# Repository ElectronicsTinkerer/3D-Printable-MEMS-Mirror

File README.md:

# 3D-Printable-MEMS-Mirror
Files for a 3D-printable MEMS mirror.

## Files
* `models` - SolidWorks files for parts
* `stls` - STL files for printing
* `arduino` - Arduino controller code
* `kicad` - PCB files (and gerbers)

## Online Resources
* [MDPI Books, _MEMS Mirrors_ ](https://www.mdpi.com/books/pdfview/book/611) - Great PDF of a lot of different MEMS mirrors designs and analysis.
* Shopping (For commercial MEMS Mirrors):
  * [Mirrorcle Technologies Inc.](https://www.mirrorcletech.com/wp/products/mems-mirrors/) - Has pricing info
  * [Preciseley Microtechnology Corp.](https://preciseley.com/products/) - Even has development hats for RPi!
  * [Hamamatsu](https://www.hamamatsu.com/us/en/product/optical-components/mems-mirror/index.html)

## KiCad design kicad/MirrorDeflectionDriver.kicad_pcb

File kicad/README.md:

# Axis Drivers for Mirrors

## Interface
### Power
Each board has a 16-30v DC, single rail input. This is the operating voltage of the output amplifiers.

### Output
At the end of the board is the output terminal block to be connected to one of the yoke's deflection coils.

### Digital Interface
At the other end is a parallel interface header for sending data to the DAC. The DAC operates over a 5v interface and all connections have 10k pullup resistors, meaning that unused inputs can be left unconnected. There is a 12-bit parallel data bus, read/write, chip select, reset, and load inputs.

## Output Drive Design
In order to achieve a differential output, two output amplifiers are used, one the inversion of the other around 0.5 * VCC.

## Known Issues
* The heatsinks currently on the KiCad boards are inadequate for the output amplifiers if running at greater than about 0.5A output current. (Active cooling is required)
* The 2.5V regulator's pinning is rotated 120 degrees clockwise from what it should be, so check the datasheet and schematic before soldering. This should be fixed some time in the future.

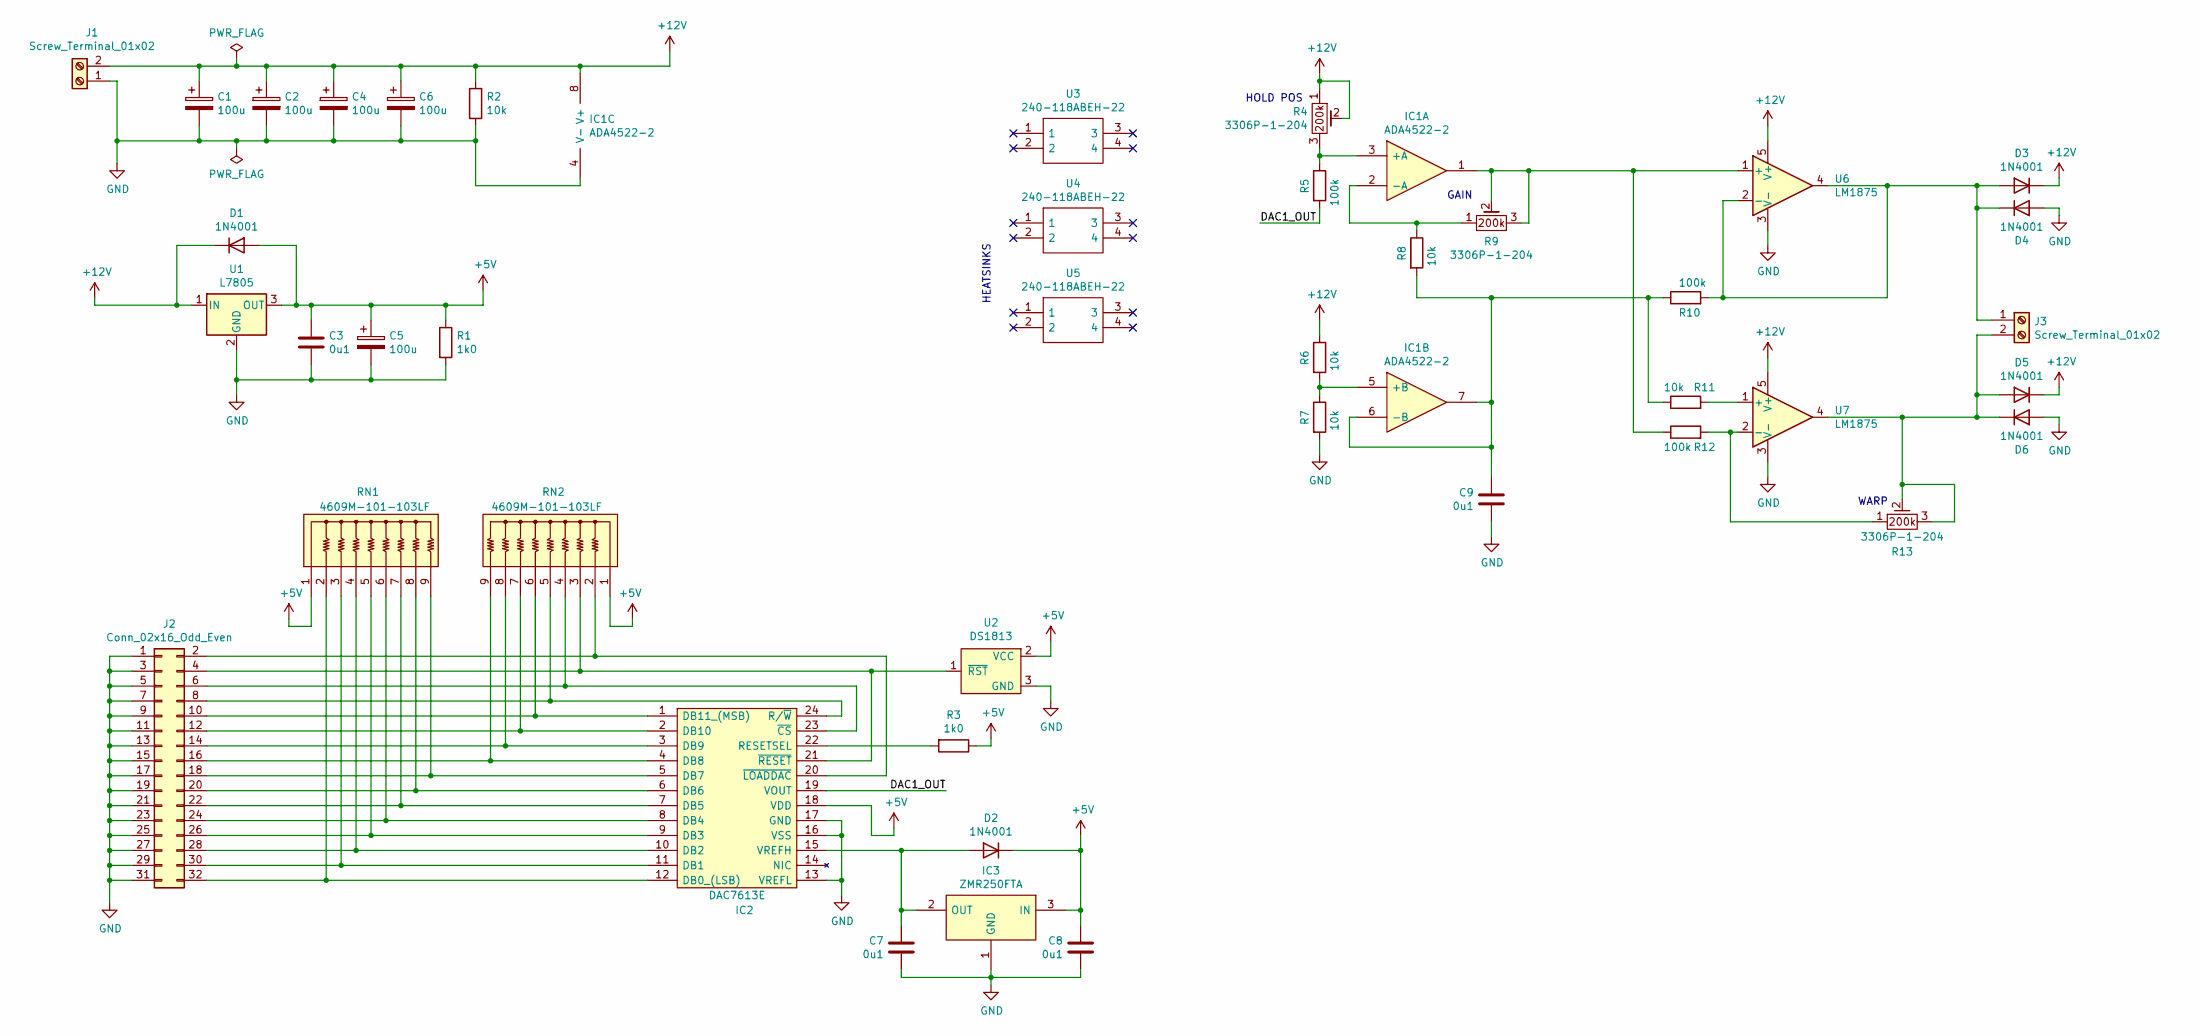
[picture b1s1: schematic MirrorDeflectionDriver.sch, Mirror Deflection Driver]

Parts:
C1, C2, C4, C5, C6: 100u; CP_Radial_D8.0mm_P3.50mm
C3, C7, C8, C9: 0u1; C_Disc_D4.3mm_W1.9mm_P5.00mm
D1, D2, D3, D4, D5, D6: 1N4001; D_DO-41_SOD81_P10.16mm_Horizontal
IC1: ADA4522-2; MSOP-8_3x3mm_P0.65mm; Mouser Part Number 584-ADA4522-2
IC2: DAC7613E; SOP65P780X200-24N; Mouser Part Number 595-DAC7613E
IC3: ZMR250FTA; SOT96P240X100-3N; Mouser Part Number 522-ZMR250FTA
J1, J3: Screw_Terminal_01x02; TerminalBlock_bornier-2_P5.08mm
J2: Conn_02x16_Odd_Even; PinHeader_2x16_P2.54mm_Vertical
R1, R3: 1k0; R_Axial_DIN0207_L6.3mm_D2.5mm_P7.62mm_Horizontal
R2, R6, R7, R8, R11: 10k; R_Axial_DIN0207_L6.3mm_D2.5mm_P7.62mm_Horizontal
R4, R9, R13: 3306P-1-204; 3306P1204; Mouser Part Number 652-3306P-1-204
R5, R10, R12: 100k; R_Axial_DIN0207_L6.3mm_D2.5mm_P7.62mm_Horizontal
RN1, RN2: 4609M-101-103LF; 4609X; Mouser Part Number 652-4609M-1LF-10K
U1: L7805; TO-126-3_Vertical
U2: DS1813; TO-92
U3, U4, U5: 240-118ABEH-22; 240118ABEH22; Mouser Part Number 567-240-118ABH-22
U6, U7: LM1875; TO-220-5_P3.4x3.7mm_StaggerOdd_Lead3.8mm_Vertical

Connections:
+5V: C3.1, C5.1, C8.1, D1.2 (A), D2.1 (K), IC2.18 (VDD), IC3.3 (IN), R1.1, R3.1, RN1.1, RN2.1, U1.3 (OUT), U2.2 (VCC)
+12V: C1.1, C2.1, C4.1, C6.1, D1.1 (K), D3.1 (K), D5.1 (K), IC1.8 (V+), J1.2, R2.1, R4.1, R4.2, R6.1, U1.1 (IN), U6.5 (V+), U7.5 (V+)
/DAC1_OUT: IC2.19 (VOUT), R5.2
GND: C1.2, C2.2, C3.2, C4.2, C5.2, C6.2, C7.2, C8.2, C9.2, D4.2 (A), D6.2 (A), IC1.4 (V-), IC2.13 (VREFL), IC2.16 (VSS), IC2.17 (GND), IC3.1 (GND), J1.1, J2.1, J2.3, J2.5, J2.7, J2.9, J2.11, J2.13, J2.15, J2.17, J2.19, J2.21, J2.23, J2.25, J2.27, J2.29, J2.31, R1.2, R2.2, R7.2, U1.2 (GND), U2.3 (GND), U6.3 (V-), U7.3 (V-)
unnamed: C7.1, D2.2 (A), IC2.15 (VREFH), IC3.2 (OUT)
unnamed: C9.1, IC1.6 (-B), IC1.7, R8.2, R10.1, R11.1
unnamed: D3.2 (A), D4.1 (K), J3.1, R10.2, U6.2 (-), U6.4
unnamed: D5.2 (A), D6.1 (K), J3.2, R13.2, R13.3, U7.4
unnamed: IC1.1, R9.2, R9.3, R12.1, U6.1 (+)
unnamed: IC1.2 (-A), R8.1, R9.1
unnamed: IC1.3 (+A), R4.3, R5.1
unnamed: IC1.5 (+B), R6.2, R7.1
unnamed: IC2.1 (DB11_(MSB)), J2.10, RN2.6
unnamed: IC2.2 (DB10), J2.12, RN2.7
unnamed: IC2.3 (DB9), J2.14, RN2.8
unnamed: IC2.4 (DB8), J2.16, RN2.9
unnamed: IC2.5 (DB7), J2.18, RN1.9
unnamed: IC2.6 (DB6), J2.20, RN1.8
unnamed: IC2.7 (DB5), J2.22, RN1.7
unnamed: IC2.8 (DB4), J2.24, RN1.6
unnamed: IC2.9 (DB3), J2.26, RN1.5
unnamed: IC2.10 (DB2), J2.28, RN1.4
unnamed: IC2.11 (DB1), J2.30, RN1.3
unnamed: IC2.12 (DB0_(LSB)), J2.32, RN1.2
unnamed: IC2.20 (~LOADDAC), J2.2, RN2.2
unnamed: IC2.21 (~RESET), J2.4, RN2.3, U2.1 (~RST)
unnamed: IC2.22 (RESETSEL), R3.2
unnamed: IC2.23 (~CS), J2.6, RN2.4
unnamed: IC2.24 (R/~W), J2.8, RN2.5
unnamed: R11.2, U7.1 (+)
unnamed: R12.2, R13.1, U7.2 (-)

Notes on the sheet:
GAIN
HOLD POS
WARP
HEATSINKS

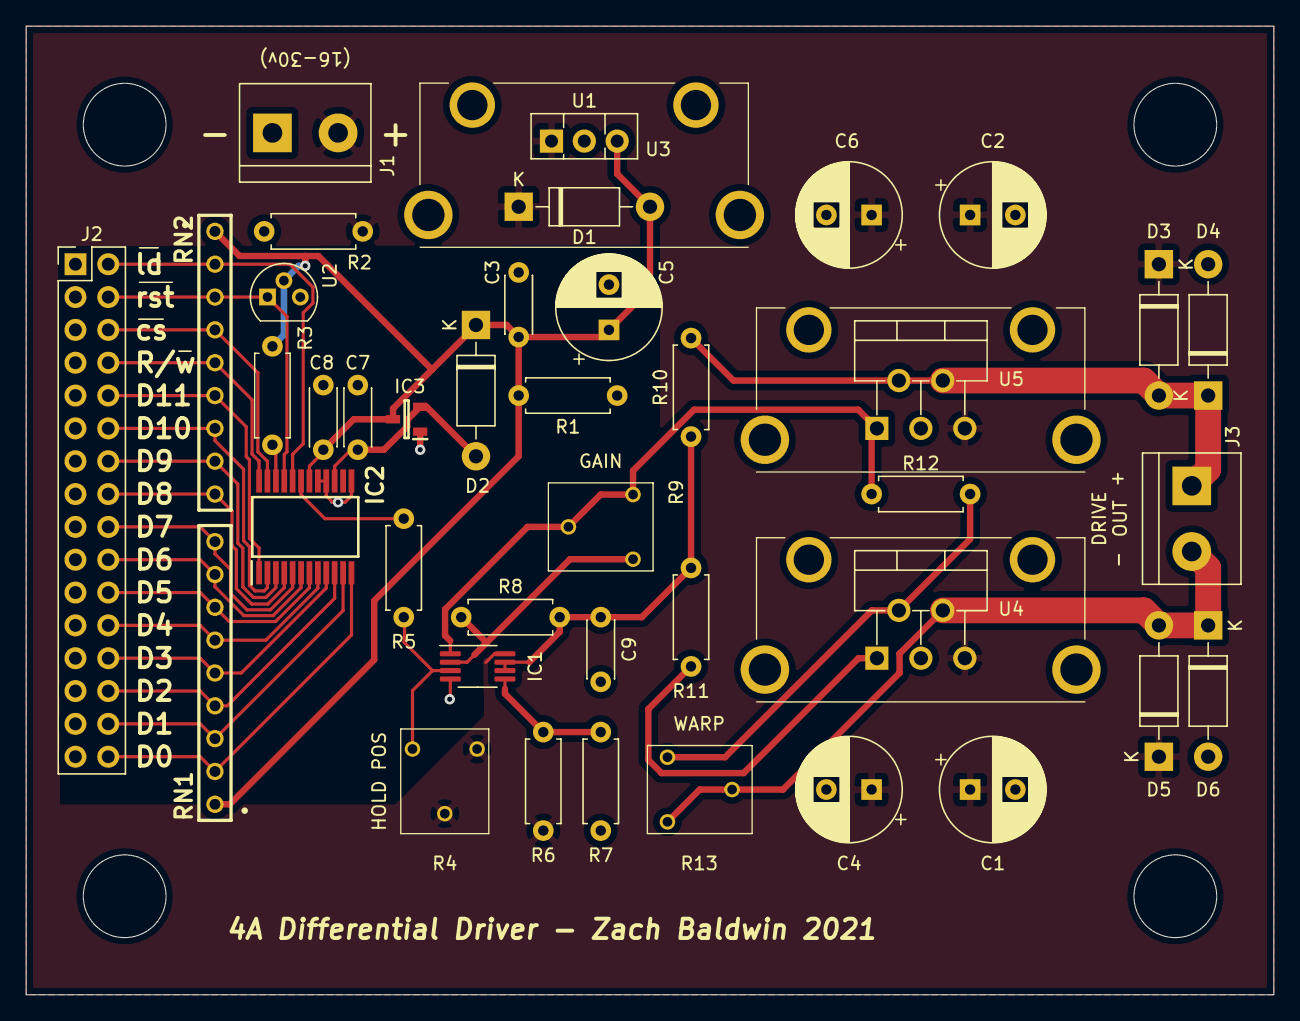
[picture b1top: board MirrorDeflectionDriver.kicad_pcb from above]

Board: 2 copper layers, 96.5 x 74.9 mm, 43 parts (0 on the bottom side), 31 nets.

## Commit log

2021-06-13 Initial addition and organization of design files
2021-06-14 Added note about regulator layout issue
2024-05-27 Re-export Schematic.pdf
